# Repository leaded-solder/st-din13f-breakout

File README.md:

# Atari ST monitor breakout
This is a small adapter meant to use an Atari ST monitor, such as the SC1224, with a different video source.

Available inputs (as of v0.1):
 - Composite video
 - RGBHV over HD15 ("VGA" port)

Additionally, all pins of the 13-pin DIN are broken out onto fingers, suitable for prototyping or adding an audio input.

# Tested With
Nothing yet... watch this space

# Bill of Materials
 - CUI SDD-130J (or AliExpress substitute)
 - Female HD15 connector
 - RCJ-017 yellow composite video jack

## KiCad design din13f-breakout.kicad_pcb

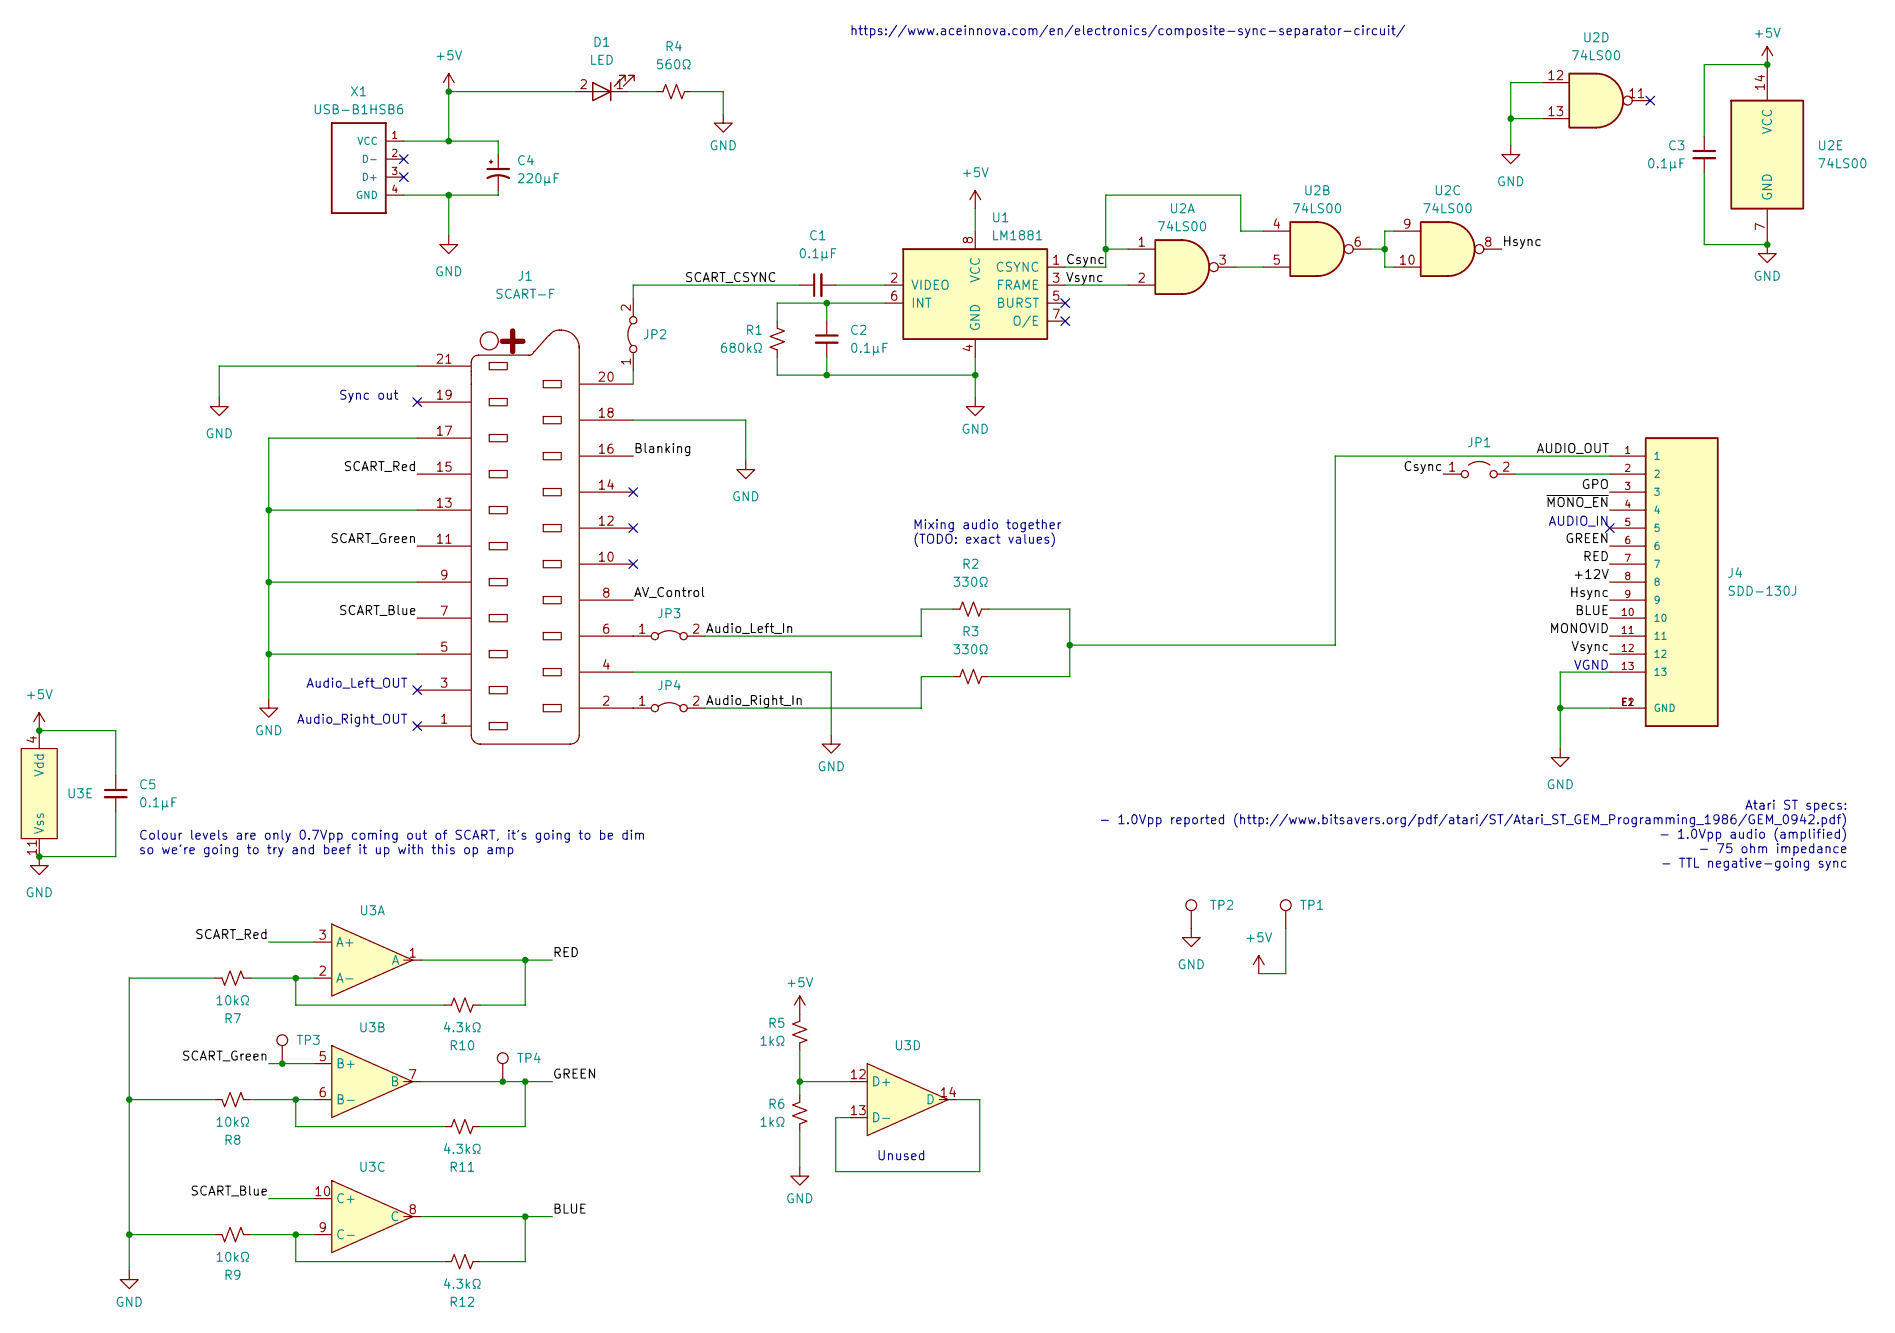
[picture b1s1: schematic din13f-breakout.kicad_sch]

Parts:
C1, C2, C3, C5: 0.1µF; C_0805_2012Metric_Pad1.18x1.45mm_HandSolder
C4: 220µF; CP_Radial_D8.0mm_P3.50mm
D1: LED; LED_D3.0mm
J1: SCART-F; NINIGI-SCART-RA
J4: SDD-130J; CUI_SDD-130J; PARTREV 1.06/02-13-2020
JP1: Jumper_2_Open; R_0805_2012Metric_Pad1.20x1.40mm_HandSolder
JP2, JP3, JP4: Jumper_2_Bridged; SolderJumper-2_P1.3mm_Bridged_RoundedPad1.0x1.5mm
R1: 680kΩ; R_0805_2012Metric_Pad1.20x1.40mm_HandSolder
R2, R3: 330Ω; R_0805_2012Metric_Pad1.20x1.40mm_HandSolder
R4: 560Ω; R_0805_2012Metric_Pad1.20x1.40mm_HandSolder
R5, R6: 1kΩ; R_0805_2012Metric_Pad1.20x1.40mm_HandSolder
R7, R8, R9: 10kΩ; R_0805_2012Metric_Pad1.20x1.40mm_HandSolder
R10, R11, R12: 4.3kΩ; R_0805_2012Metric_Pad1.20x1.40mm_HandSolder
TP1, TP2, TP3, TP4: TestPoint; TestPoint_Loop_D2.50mm_Drill1.0mm
U1: LM1881; SOIC-8_3.9x4.9mm_P1.27mm
U2: 74LS00; SOIC-14_3.9x8.7mm_P1.27mm
U3: MCP6499; SOIC-14_3.9x8.7mm_P1.27mm
X1: USB-B1HSB6; OST_USB-B1HSB6; DigiKey ED2983-ND

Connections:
+5V: C3.1, C4.1, C5.1, D1.2 (A), R5.1, TP1.1, U1.8 (VCC), U2.14 (VCC), U3.4 (Vdd), X1.1 (VCC)
/+12V: J4.8
/AUDIO_OUT: J4.1, R2.2, R3.2
/AV_Control: J1.8
/Audio_Left_In: JP3.2 (B), R2.1
/Audio_Right_In: JP4.2 (B), R3.1
/BLUE: J4.10, R12.2, U3.8 (C)
/Blanking: J1.16
/Csync: JP1.1 (A), U1.1 (CSYNC), U2.1, U2.4
/GPO: J4.3
/GREEN: J4.6, R11.2, TP4.1, U3.7 (B)
/Hsync: J4.9, U2.8
/MONOVID: J4.11
/RED: J4.7, R10.2, U3.1 (A)
/SCART_Blue: J1.7, U3.10 (C+)
/SCART_CSYNC: C1.1, JP2.2 (B)
/SCART_Green: J1.11, TP3.1, U3.5 (B+)
/SCART_Red: J1.15, U3.3 (A+)
/Vsync: J4.12, U1.3 (FRAME), U2.2
/~MONO_EN: J4.4
GND: C2.2, C3.2, C4.2, C5.2, J1.4, J1.5, J1.9, J1.13, J1.17, J1.18, J1.21, J4.13, J4.E1 (GND), J4.E2 (GND), R1.2, R4.2, R6.2, R7.1, R8.1, R9.1, TP2.1, U1.4 (GND), U2.7 (GND), U2.12, U2.13, U3.11 (Vss), X1.4 (GND)
unnamed: D1.1 (K), R4.1
unnamed: J1.2, JP4.1 (A)
unnamed: J1.6, JP3.1 (A)
unnamed: J1.20, JP2.1 (A)
unnamed: J4.2, JP1.2 (B)
unnamed: C2.1, R1.1, U1.6 (INT)
unnamed: C1.2, U1.2 (VIDEO)
unnamed: U2.3, U2.5
unnamed: U2.6, U2.9, U2.10
unnamed: R7.2, R10.1, U3.2 (A-)
unnamed: R8.2, R11.1, U3.6 (B-)
unnamed: R9.2, R12.1, U3.9 (C-)
unnamed: U3.13 (D-), U3.14 (D)
unnamed: R5.2, R6.1, U3.12 (D+)

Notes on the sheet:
Audio_Right_OUT
Audio_Left_OUT
Colour levels are only 0.7Vpp coming out of SCART, it's going to be dim so we're going to try and beef it up with this op amp
Unused
Atari ST specs: - 1.0Vpp reported (http://www.bitsavers.org/pdf/atari/ST/Atari_ST_GEM_Programming_1986/GEM_0942.pdf) - 1.0Vpp audio (amplified) - 75 ohm impedance - TTL negative-going sync
Mixing audio together (TODO: exact values)
Sync out
https://www.aceinnova.com/en/electronics/composite-sync-separator-circuit/
AUDIO_IN
VGND

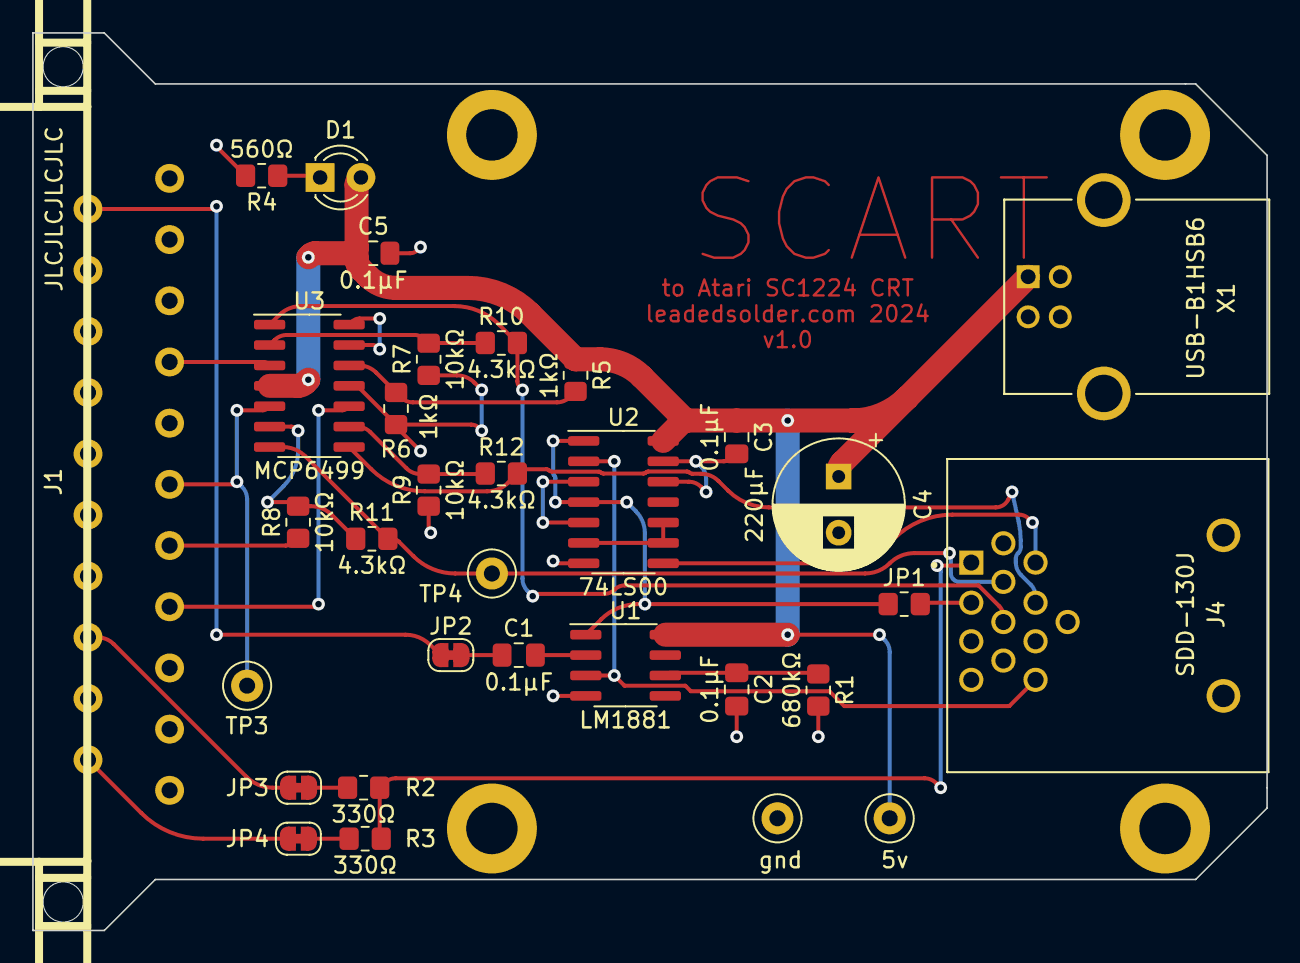
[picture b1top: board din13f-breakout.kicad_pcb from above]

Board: 2 copper layers, 76.8 x 55.9 mm, 32 parts (0 on the bottom side), 29 nets.

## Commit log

2022-04-08 v0.1
2022-05-10 v0.1 board
2022-05-10 README
2022-05-10 Updated BOM
2024-03-14 Upgrade KiCad
2024-03-14 Draft of SCART version, no RGB voltage ampl yet
2024-03-22 WIP for op-amps
2024-03-22 Bypass cap for amp
2024-03-22 No more DIP
2024-04-04 Laying out the birdseed
2024-04-04 Fully popped
2024-04-04 Rounded tracks
2024-04-04 Fix missing Vsync
2024-04-05 V1 sent to fab
